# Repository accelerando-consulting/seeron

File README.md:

# The Eye of Seeron

A better illuminated loupe for inspecting circuit boards.

I bought [this loupe](https://s.click.aliexpress.com/e/_Dc7G7sf) for
inspecting circuit boards, because of its built in LEDs.   But there
is a risk of depleting the coin cell batteries if it is left on, so I 
wanted to fit a rechargeable power source.   I began by attempting to
modify the existing circuitry, but it is extremely difficult to solder
to the existing circuit board, due to it being surrounded by a welded
plastic shell.

So I removed the existing circuitry and LEDs entirely and created a
ring-light that fits underneath the existing lens retaining ring.

You will need some way of limiting the current draw to no more than
about 200mA.  Either fit a resistor in series with the battery, or
stay tuned for my auto-off control circuit.

The circuit needs up to twelve surface mount Light-Emitting Diodes
(LED) in size 0603.   I used six normal LEDs ([LCSC part C965808](https://www.lcsc.com/product-detail/LED-Indication-Discrete_XINGLIGHT-XL-1608UWC-04_C965808.html))
 and six side-emitting type ([LCSC part
 C273618](https://www.lcsc.com/product-detail/LED-Indication-Discrete_TOGIALED-TJ-S1706SW6TGLCCW-A5_C273618.html).

## I want to make one 

You can upload the gerbers.zip file to JLCPCB to have this made, or
use the mill_gerbers.zip to cut your own on a CNC mill.

You can find instructions for the milling process [here](https://accelerando.com.au/news/2021/07/how-we-make-fast-prototypes-at-accelerando-part-1-pcbs/).

## Can I just buy one off you?

Soon.
.

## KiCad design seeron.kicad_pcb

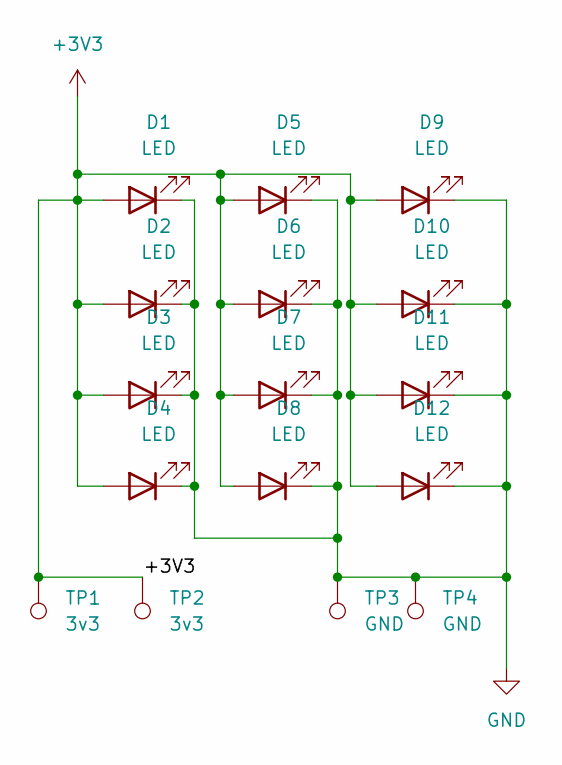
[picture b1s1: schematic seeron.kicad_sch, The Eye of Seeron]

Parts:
D1, D2, D3, D4, D5, D6, D7, D8, D9, D10, D11, D12: LED; LED_0603_1608Metric
TP1, TP2: 3v3; TestPoint_Pad_D1.0mm
TP3, TP4: GND; TestPoint_Pad_D1.0mm

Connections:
+3V3: D1.2 (A), D2.2 (A), D3.2 (A), D4.2 (A), D5.2 (A), D6.2 (A), D7.2 (A), D8.2 (A), D9.2 (A), D10.2 (A), D11.2 (A), D12.2 (A), TP1.1, TP2.1
GND: D1.1 (K), D2.1 (K), D3.1 (K), D4.1 (K), D5.1 (K), D6.1 (K), D7.1 (K), D8.1 (K), D9.1 (K), D10.1 (K), D11.1 (K), D12.1 (K), TP3.1, TP4.1

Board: 2 copper layers, 16 parts (0 on the bottom side), 2 nets, no tracks yet.

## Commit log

2024-09-19 Single sided ringlight PCB for 25.4mm loupe
2024-09-19 Add readme and more test points for providing power contacts if solder mask is used
2024-09-19 Add images
